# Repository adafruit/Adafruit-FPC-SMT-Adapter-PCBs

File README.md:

## Adafruit FPC SMT Adapter PCBs
&nbsp; 
&nbsp; 
<br />
Click to purchase from the Adafruit Shop:
- [Adafruit FPC Stick - 20 Pin 0.5mm/1.0mm Pitch Adapter](https://www.adafruit.com/product/1325)
- [Adafruit Multi-pitch FPC Adapter - 40 Pin 0.5/0.6/0.7/0.8/1.0mm](https://www.adafruit.com/product/1436)
- [Adafruit 50 pin 0.5mm pitch FPC Adapter](https://www.adafruit.com/product/1492)

Connect to 0.5mm, 1.0mm and even some 2.0mm pitch connectors that you may run across with an FPC stick. We designed this for use in house, to quickly connect to FPCs we need to test. But we also thought it might be useful for our customers. On either side is a 20 pin 0.5 or 1.0mm pitch connector with long pads and one very long 'mechanical' pad. Each pad is broken out to a 20-pin long 0.1" spaced header. It can accommodate most ZIF and snap connectors and will make prototyping much easier on you!

You will roll lucky 7's and connect to nearly any kind of FPC/flex cable with Ladyada's Super Lucky 40-pin FPC to breadboard adapter plate. You get 40 pads of 0.5mm, 0.6mm, 0.7mm, 0.8mm or 1.0mm. It may even work for some 2.0mm pitch connectors. We designed this for use in house, to quickly connect to FPCs we need to test. But we also thought it might be useful for our customers. Each pad is broken out to both a 2x20 0.1" spaced header as well as two strips of 20-pin long 0.1" spaced header 2.1" inches apart. It can accommodate most ZIF and snap connectors or just solder the FPC directly on. This adapter will make prototyping much easier on you!

Connect to those pesky 0.5mm pitch connectors that you may run across with an FPC stick. We designed this for use in house, to quickly connect to 50pin 0.5mm pitch flex cables we need to test. But we also thought it might be useful for our customers. There's a 50-pin long connector on top, and we have one very long 'mechanical' pad. Since the pad extends along the entire length you can use any size 0.5mm pitch connector you wish, we seem to bump into 40 and 50 pin the most. Each pad is broken out to a 25-pin long 0.1"x0.1" spaced header. One side is doubled on the opposite side to make it bread-board friendly. It can accommodate most ZIF and snap connectors and will make prototyping much easier on you!

For more details, check out the product pages at
- http://www.adafruit.com/products/1325
- http://www.adafruit.com/products/1436
- http://www.adafruit.com/products/1492

PCB files for Adafruit FPC SMT Adapter Breakout Boards. The format is EagleCAD schematic and board layout

### License

Adafruit invests time and resources providing this open source design, please support Adafruit and open-source hardware by purchasing products from [Adafruit](https://www.adafruit.com)!

All text above must be included in any redistribution

Designed by Limor Fried/Ladyada for Adafruit Industries.
Creative Commons Attribution/Share-Alike, all text above must be included in any redistribution. 
See license.txt for additional information.

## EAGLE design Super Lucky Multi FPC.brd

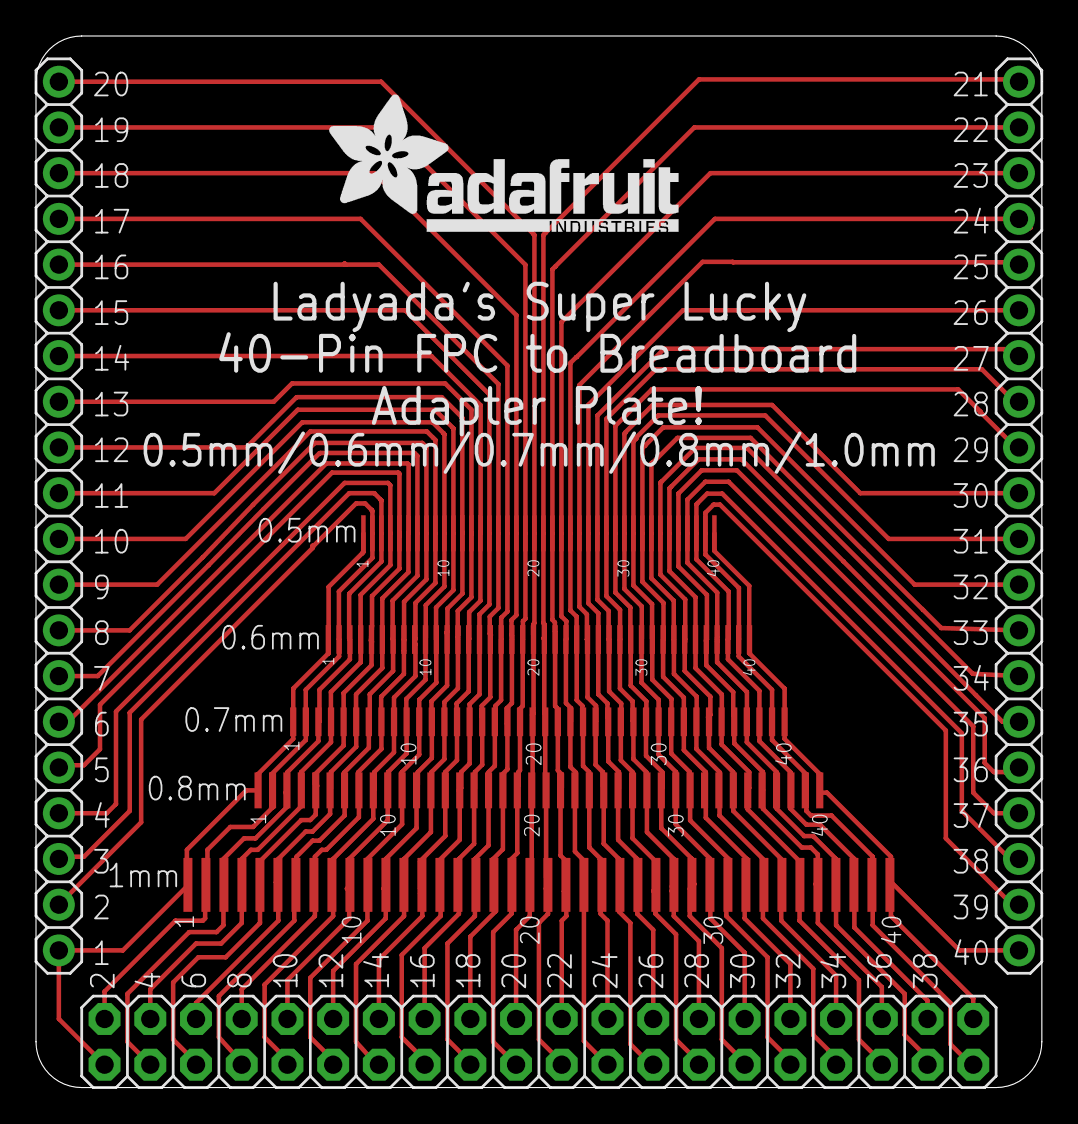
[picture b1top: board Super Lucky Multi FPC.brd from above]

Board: 2 copper layers, 55.9 x 58.4 mm, 9 parts (0 on the bottom side), 40 nets.

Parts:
CON1: PINHD-1X40-0.5MM; 1X40-0.5MM
JP1: 2X20-BIG
JP2, JP3: 1X20-BIG
U$1: PINHD-1X40-0.6MM; 1X40-0.6MM
U$2: PINHD-1X40-0.7MM; 1X40-0.7MM
U$3: PINHD-1X40-0.8MM; 1X40-0.8MM
U$4: PINHD-1X40-1MM; 1X40-1MM
U$5: ADAFRUIT_TEXT_20MM

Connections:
unnamed: CON1.1, JP1.1, JP2.1, U$1.1, U$2.1, U$3.1, U$4.1
unnamed: CON1.2, JP1.2, JP2.2, U$1.2, U$2.2, U$3.2, U$4.2
unnamed: CON1.3, JP1.3, JP2.3, U$1.3, U$2.3, U$3.3, U$4.3
unnamed: CON1.4, JP1.4, JP2.4, U$1.4, U$2.4, U$3.4, U$4.4
unnamed: CON1.5, JP1.5, JP2.5, U$1.5, U$2.5, U$3.5, U$4.5
unnamed: CON1.6, JP1.6, JP2.6, U$1.6, U$2.6, U$3.6, U$4.6
unnamed: CON1.7, JP1.7, JP2.7, U$1.7, U$2.7, U$3.7, U$4.7
unnamed: CON1.8, JP1.8, JP2.8, U$1.8, U$2.8, U$3.8, U$4.8
unnamed: CON1.9, JP1.9, JP2.9, U$1.9, U$2.9, U$3.9, U$4.9
unnamed: CON1.10, JP1.10, JP2.10, U$1.10, U$2.10, U$3.10, U$4.10
unnamed: CON1.11, JP1.11, JP2.11, U$1.11, U$2.11, U$3.11, U$4.11
unnamed: CON1.12, JP1.12, JP2.12, U$1.12, U$2.12, U$3.12, U$4.12
unnamed: CON1.13, JP1.13, JP2.13, U$1.13, U$2.13, U$3.13, U$4.13
unnamed: CON1.14, JP1.14, JP2.14, U$1.14, U$2.14, U$3.14, U$4.14
unnamed: CON1.15, JP1.15, JP2.15, U$1.15, U$2.15, U$3.15, U$4.15
unnamed: CON1.16, JP1.16, JP2.16, U$1.16, U$2.16, U$3.16, U$4.16
unnamed: CON1.17, JP1.17, JP2.17, U$1.17, U$2.17, U$3.17, U$4.17
unnamed: CON1.18, JP1.18, JP2.18, U$1.18, U$2.18, U$3.18, U$4.18
unnamed: CON1.19, JP1.19, JP2.19, U$1.19, U$2.19, U$3.19, U$4.19
unnamed: CON1.20, JP1.20, JP2.20, U$1.20, U$2.20, U$3.20, U$4.20
unnamed: CON1.21, JP1.21, JP3.1, U$1.21, U$2.21, U$3.21, U$4.21
unnamed: CON1.22, JP1.22, JP3.2, U$1.22, U$2.22, U$3.22, U$4.22
unnamed: CON1.23, JP1.23, JP3.3, U$1.23, U$2.23, U$3.23, U$4.23
unnamed: CON1.24, JP1.24, JP3.4, U$1.24, U$2.24, U$3.24, U$4.24
unnamed: CON1.25, JP1.25, JP3.5, U$1.25, U$2.25, U$3.25, U$4.25
unnamed: CON1.26, JP1.26, JP3.6, U$1.26, U$2.26, U$3.26, U$4.26
unnamed: CON1.27, JP1.27, JP3.7, U$1.27, U$2.27, U$3.27, U$4.27
unnamed: CON1.28, JP1.28, JP3.8, U$1.28, U$2.28, U$3.28, U$4.28
unnamed: CON1.29, JP1.29, JP3.9, U$1.29, U$2.29, U$3.29, U$4.29
unnamed: CON1.30, JP1.30, JP3.10, U$1.30, U$2.30, U$3.30, U$4.30
unnamed: CON1.31, JP1.31, JP3.11, U$1.31, U$2.31, U$3.31, U$4.31
unnamed: CON1.32, JP1.32, JP3.12, U$1.32, U$2.32, U$3.32, U$4.32
unnamed: CON1.33, JP1.33, JP3.13, U$1.33, U$2.33, U$3.33, U$4.33
unnamed: CON1.34, JP1.34, JP3.14, U$1.34, U$2.34, U$3.34, U$4.34
unnamed: CON1.35, JP1.35, JP3.15, U$1.35, U$2.35, U$3.35, U$4.35
unnamed: CON1.36, JP1.36, JP3.16, U$1.36, U$2.36, U$3.36, U$4.36
unnamed: CON1.37, JP1.37, JP3.17, U$1.37, U$2.37, U$3.37, U$4.37
unnamed: CON1.38, JP1.38, JP3.18, U$1.38, U$2.38, U$3.38, U$4.38
unnamed: CON1.39, JP1.39, JP3.19, U$1.39, U$2.39, U$3.39, U$4.39
unnamed: CON1.40, JP1.40, JP3.20, U$1.40, U$2.40, U$3.40, U$4.40

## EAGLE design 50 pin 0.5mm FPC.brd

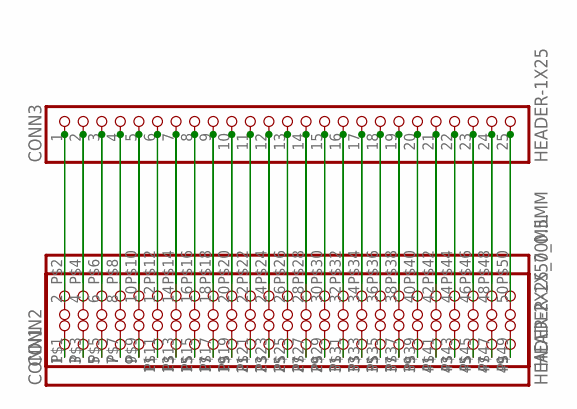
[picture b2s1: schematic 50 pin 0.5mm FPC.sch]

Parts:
CONN1: HEADER-2X25_70MIL; 2X25
CONN2: HEADER-1X50_0.5MM; FPC_GENERIC_0.5MM_50PIN
CONN3: HEADER-1X25; 1X25_ROUND_70MIL

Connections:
unnamed: CONN1.1, CONN2.P$1 (1)
unnamed: CONN1.2, CONN2.P$2 (2), CONN3.1
unnamed: CONN1.3, CONN2.P$3 (3)
unnamed: CONN1.4, CONN2.P$4 (4), CONN3.2
unnamed: CONN1.5, CONN2.P$5 (5)
unnamed: CONN1.6, CONN2.P$6 (6), CONN3.3
unnamed: CONN1.7, CONN2.P$7 (7)
unnamed: CONN1.8, CONN2.P$8 (8), CONN3.4
unnamed: CONN1.9, CONN2.P$9 (9)
unnamed: CONN1.10, CONN2.P$10 (10), CONN3.5
unnamed: CONN1.11, CONN2.P$11 (11)
unnamed: CONN1.12, CONN2.P$12 (12), CONN3.6
unnamed: CONN1.13, CONN2.P$13 (13)
unnamed: CONN1.14, CONN2.P$14 (14), CONN3.7
unnamed: CONN1.15, CONN2.P$15 (15)
unnamed: CONN1.16, CONN2.P$16 (16), CONN3.8
unnamed: CONN1.17, CONN2.P$17 (17)
unnamed: CONN1.18, CONN2.P$18 (18), CONN3.9
unnamed: CONN1.19, CONN2.P$19 (19)
unnamed: CONN1.20, CONN2.P$20 (20), CONN3.10
unnamed: CONN1.21, CONN2.P$21 (21)
unnamed: CONN1.22, CONN2.P$22 (22), CONN3.11
unnamed: CONN1.23, CONN2.P$23 (23)
unnamed: CONN1.24, CONN2.P$24 (24), CONN3.12
unnamed: CONN1.25, CONN2.P$25 (25)
unnamed: CONN1.26, CONN2.P$26 (26), CONN3.13
unnamed: CONN1.27, CONN2.P$27 (27)
unnamed: CONN1.28, CONN2.P$28 (28), CONN3.14
unnamed: CONN1.29, CONN2.P$29 (29)
unnamed: CONN1.30, CONN2.P$30 (30), CONN3.15
unnamed: CONN1.31, CONN2.P$31 (31)
unnamed: CONN1.32, CONN2.P$32 (32), CONN3.16
unnamed: CONN1.33, CONN2.P$33 (33)
unnamed: CONN1.34, CONN2.P$34 (34), CONN3.17
unnamed: CONN1.35, CONN2.P$35 (35)
unnamed: CONN1.36, CONN2.P$36 (36), CONN3.18
unnamed: CONN1.37, CONN2.P$37 (37)
unnamed: CONN1.38, CONN2.P$38 (38), CONN3.19
unnamed: CONN1.39, CONN2.P$39 (39)
unnamed: CONN1.40, CONN2.P$40 (40), CONN3.20
unnamed: CONN1.41, CONN2.P$41 (41)
unnamed: CONN1.42, CONN2.P$42 (42), CONN3.21
unnamed: CONN1.43, CONN2.P$43 (43)
unnamed: CONN1.44, CONN2.P$44 (44), CONN3.22
unnamed: CONN1.45, CONN2.P$45 (45)
unnamed: CONN1.46, CONN2.P$46 (46), CONN3.23
unnamed: CONN1.47, CONN2.P$47 (47)
unnamed: CONN1.48, CONN2.P$48 (48), CONN3.24
unnamed: CONN1.49, CONN2.P$49 (49)
unnamed: CONN1.50, CONN2.P$50 (50), CONN3.25

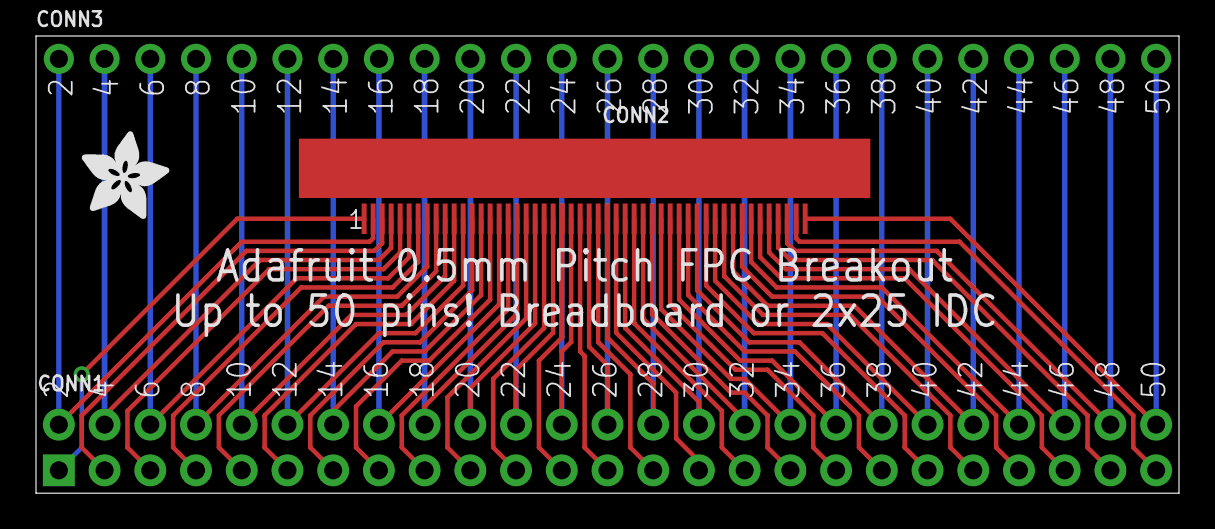
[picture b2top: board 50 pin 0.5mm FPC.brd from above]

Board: 2 copper layers, 63.5 x 25.4 mm, 4 parts (0 on the bottom side), 50 nets.

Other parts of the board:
U$1: ADAFRUIT_5MM

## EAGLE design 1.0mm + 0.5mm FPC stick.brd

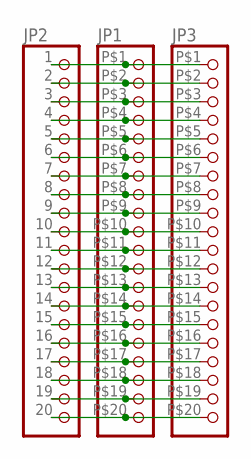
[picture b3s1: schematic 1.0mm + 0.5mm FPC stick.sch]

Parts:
JP1: HEADER-1X20FPC_1.0MM; FPC_GENERIC_1.0MM_20PIN
JP2: HEADER-1X20ROUND; 1X20_ROUND
JP3: HEADER-1X20FPC_0.5MM; FPC_GENERIC_0.5MM_20PIN

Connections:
unnamed: JP1.P$1 (1), JP2.1, JP3.P$1 (1)
unnamed: JP1.P$2 (2), JP2.2, JP3.P$2 (2)
unnamed: JP1.P$3 (3), JP2.3, JP3.P$3 (3)
unnamed: JP1.P$4 (4), JP2.4, JP3.P$4 (4)
unnamed: JP1.P$5 (5), JP2.5, JP3.P$5 (5)
unnamed: JP1.P$6 (6), JP2.6, JP3.P$6 (6)
unnamed: JP1.P$7 (7), JP2.7, JP3.P$7 (7)
unnamed: JP1.P$8 (8), JP2.8, JP3.P$8 (8)
unnamed: JP1.P$9 (9), JP2.9, JP3.P$9 (9)
unnamed: JP1.P$10 (10), JP2.10, JP3.P$10 (10)
unnamed: JP1.P$11 (11), JP2.11, JP3.P$11 (11)
unnamed: JP1.P$12 (12), JP2.12, JP3.P$12 (12)
unnamed: JP1.P$13 (13), JP2.13, JP3.P$13 (13)
unnamed: JP1.P$14 (14), JP2.14, JP3.P$14 (14)
unnamed: JP1.P$15 (15), JP2.15, JP3.P$15 (15)
unnamed: JP1.P$16 (16), JP2.16, JP3.P$16 (16)
unnamed: JP1.P$17 (17), JP2.17, JP3.P$17 (17)
unnamed: JP1.P$18 (18), JP2.18, JP3.P$18 (18)
unnamed: JP1.P$19 (19), JP2.19, JP3.P$19 (19)
unnamed: JP1.P$20 (20), JP2.20, JP3.P$20 (20)

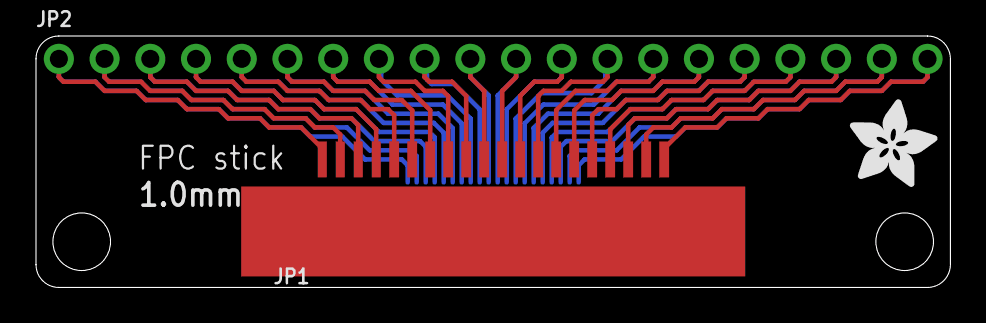
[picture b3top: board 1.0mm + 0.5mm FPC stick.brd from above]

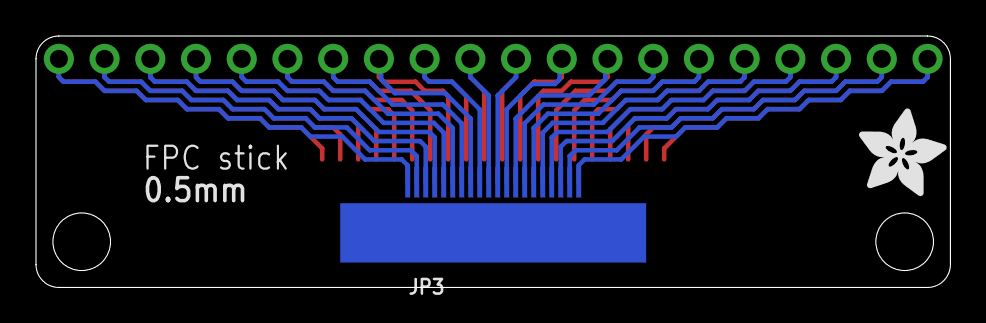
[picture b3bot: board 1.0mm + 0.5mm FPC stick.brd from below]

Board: 2 copper layers, 50.8 x 14.0 mm, 5 parts (2 on the bottom side), 20 nets.

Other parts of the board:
U$2, U$3: ADAFRUIT_5MM

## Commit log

2016-09-14 All FPC adapt0z

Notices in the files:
parts and their libraries:
microbuilder: This work is placed in the public domain, and may be freely used for commercial and non-commercial work with the following conditions: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
